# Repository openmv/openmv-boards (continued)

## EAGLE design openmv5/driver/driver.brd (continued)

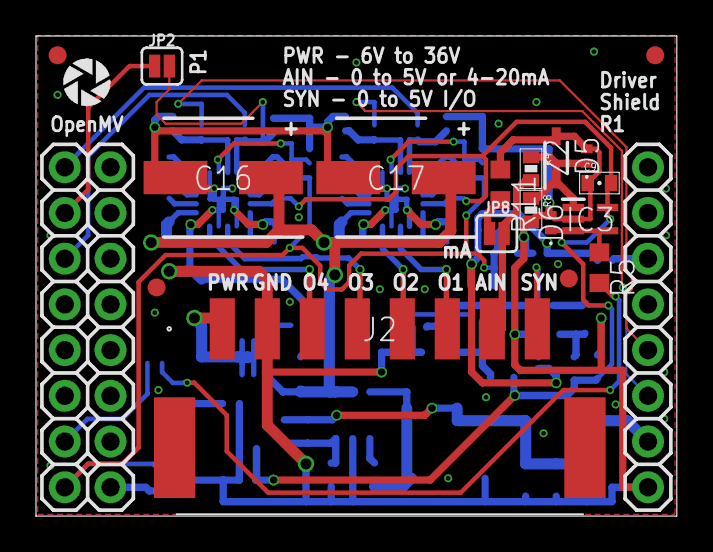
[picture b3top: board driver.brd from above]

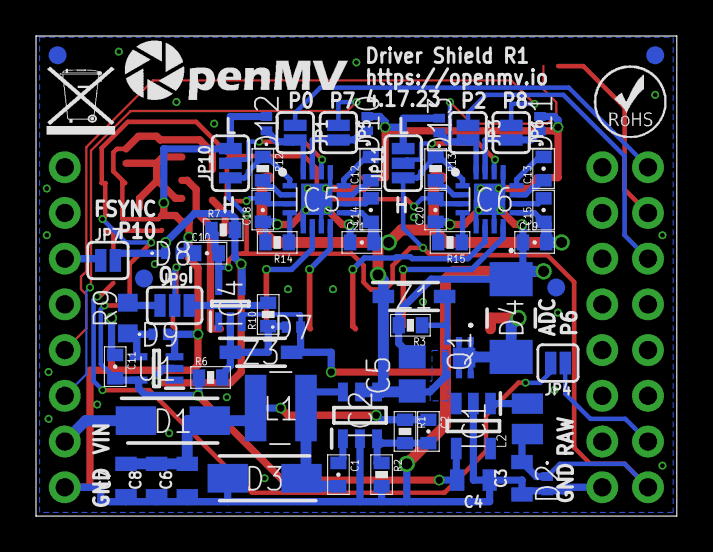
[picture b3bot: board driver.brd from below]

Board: 2 copper layers, 35.6 x 26.7 mm, 87 parts (67 on the bottom side), 50 nets.

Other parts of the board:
U$1: WEEE
U$2: ROHS
U$3: OMV-LOGO
U$9: OPENMV-LOGO

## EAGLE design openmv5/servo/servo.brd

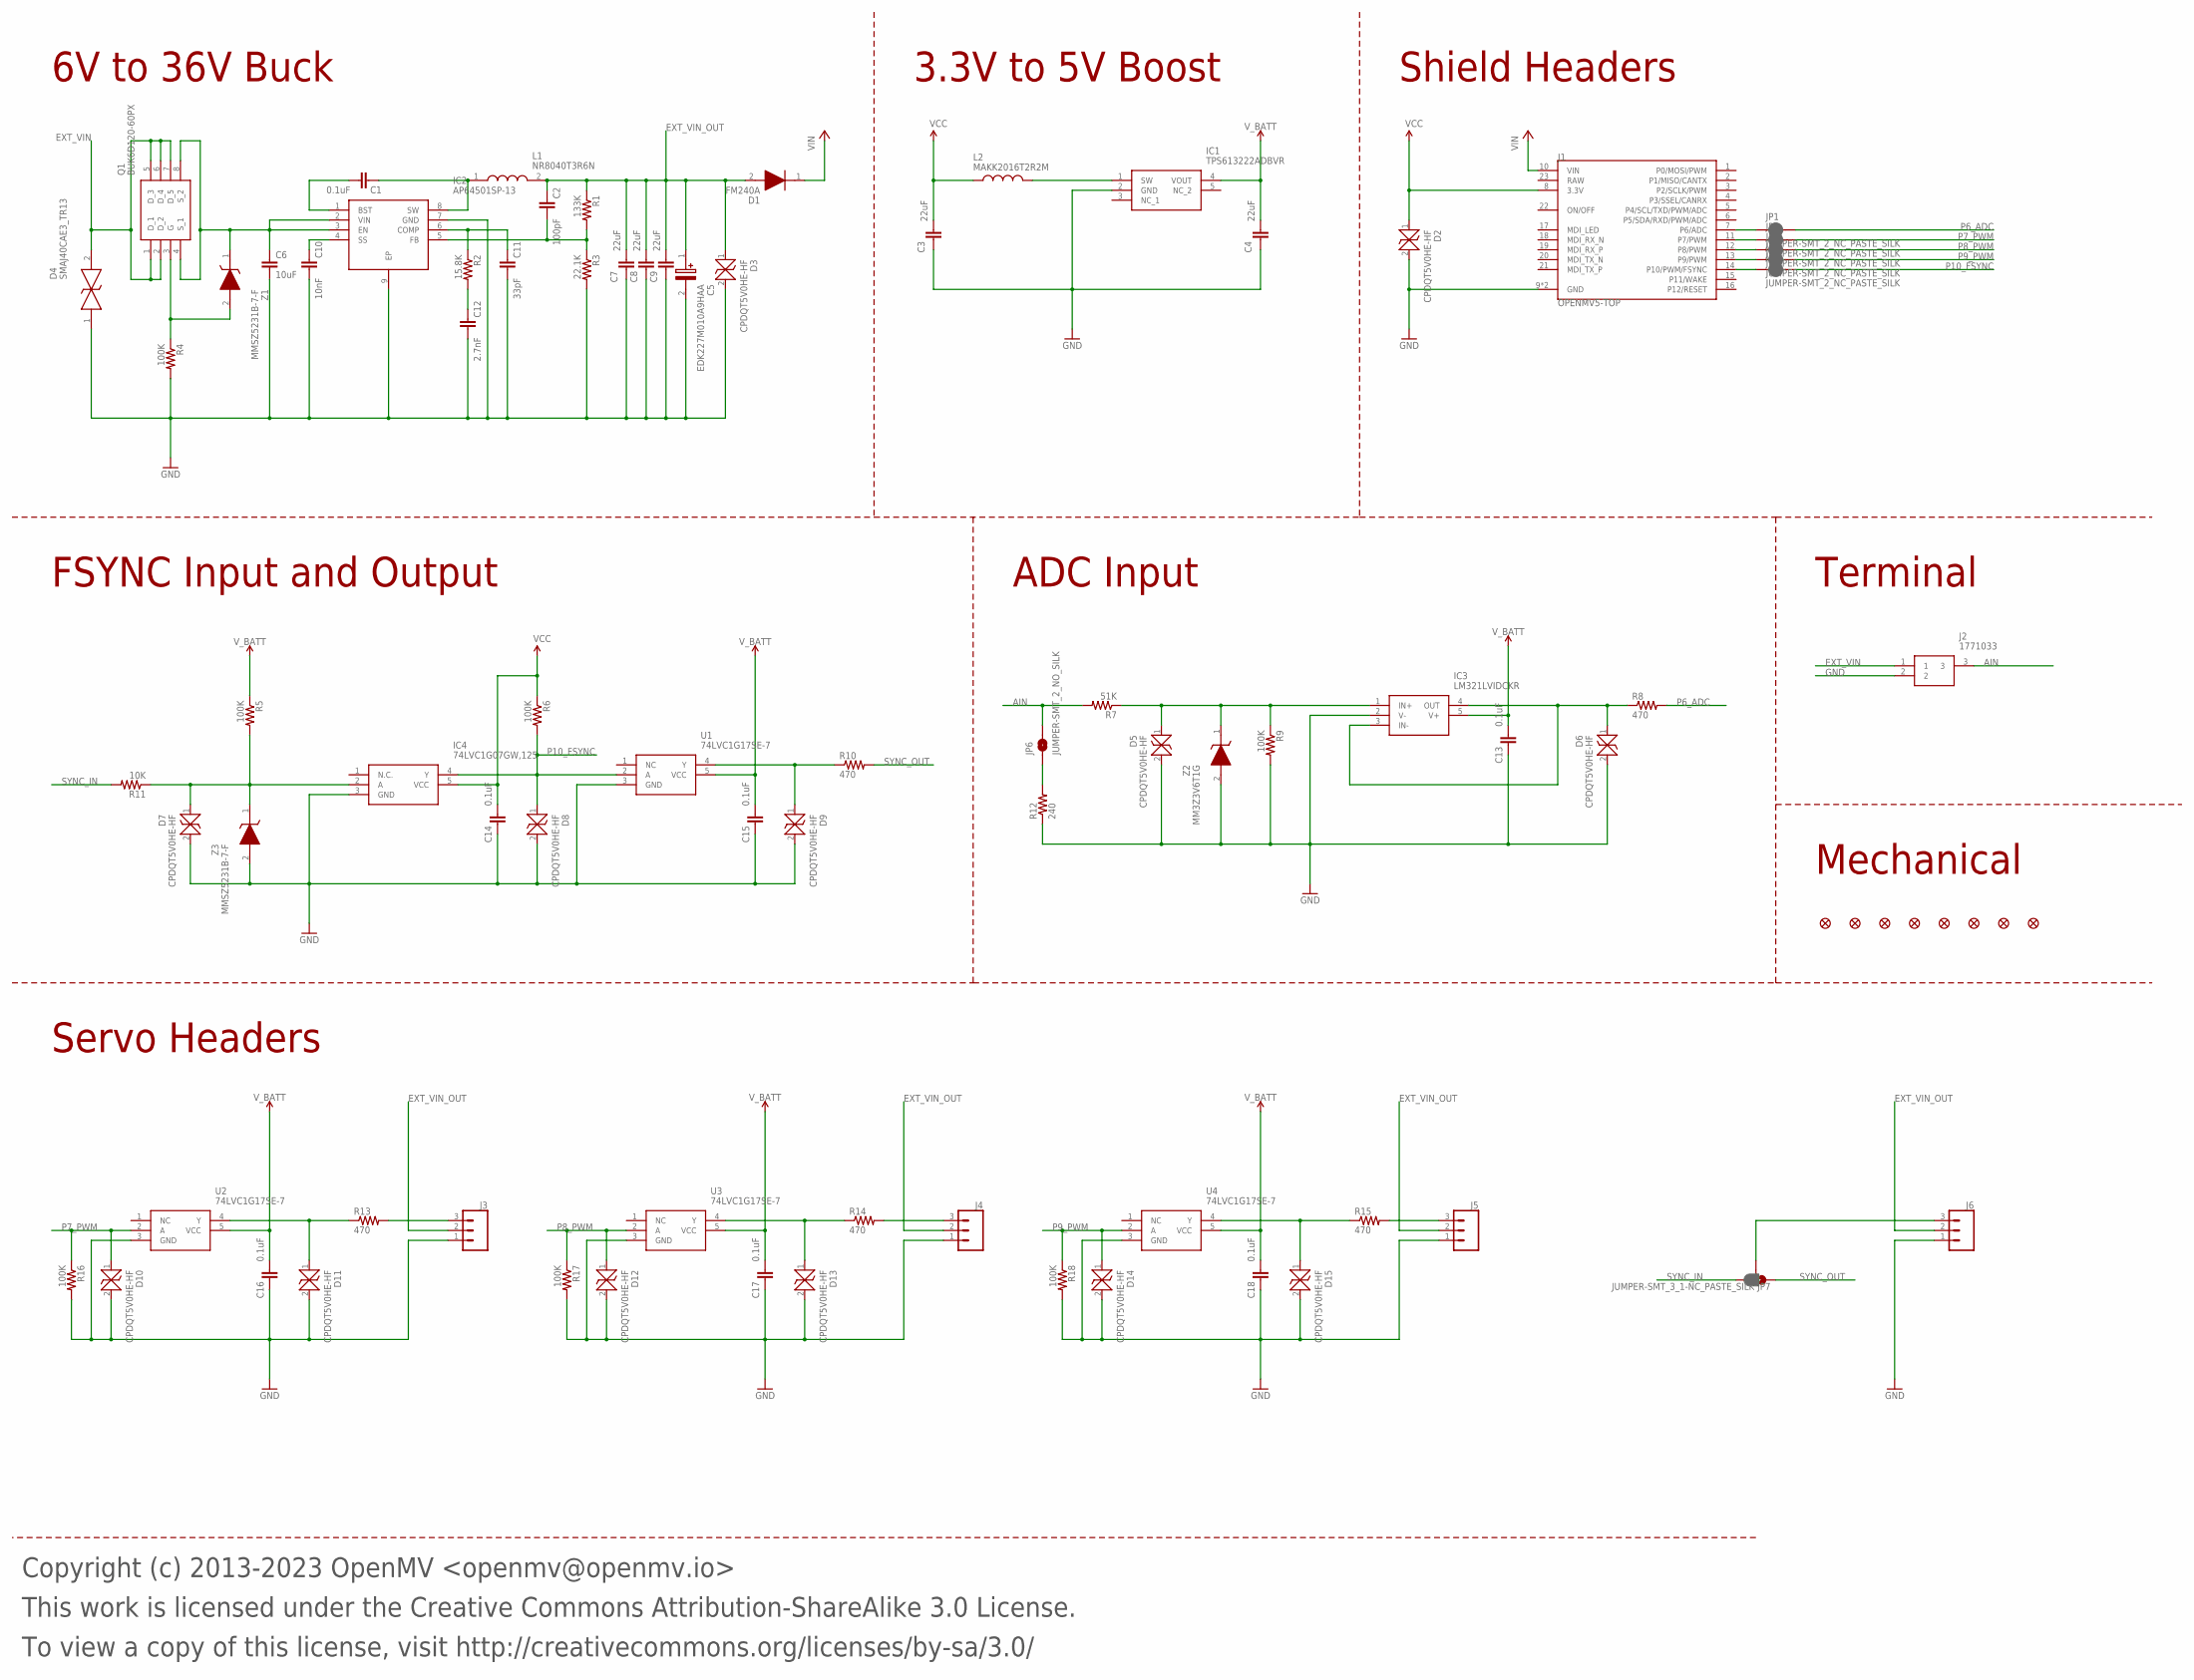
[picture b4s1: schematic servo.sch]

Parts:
C1, C13, C14, C15, C16, C17, C18: 0.1uF; 0402; MPN GRM155R71H104KE14D
C2: 100pF; 0402; MPN CC0402JRNPO9BN101
C3, C4, C7, C8, C9: 22uF; 0805; MPN CL21A226MQQNNNE
C5: EDK227M010A9HAA; CAPAE660X800N; MPN EDK227M010A9HAA
C6: 10uF; C0805; MPN GRM21BR61H106KE43K
C10: 10nF; 0402; MPN CL05B103KB5NNNC
C11: 33pF; 0402; MPN 04025A330JAT2A
C12: 2.7nF; 0402; MPN GCM155R71H272KA37J
D1: FM240A; DIOM5025X231N; MPN FM240A
D2, D3, D5, D6, D7, D8, D9, D10, D11, D12, D13, D14, D15: CPDQT5V0HE-HF; CPDQT5V0HEHF; MPN CPDQT5V0HE-HF
D4: SMAJ40CAE3_TR13; SMAJ40CAE3TR13; MPN SMAJ40CAe3/TR13
FD1, FD2, FD3, FD4, FD5, FD6, FD7, FD8: FIDUCIAL1X2; FIDUCIAL-1X2
IC1: TPS613222ADBVR; SOT95P280X145-5N; MPN TPS613222ADBVR
IC2: AP64501SP-13; SOIC127P600X163-9N; MPN AP64501SP-13
IC3: LM321LVIDCKR; SOT65P210X110-5N; MPN LM321LVIDCKR
IC4: 74LVC1G07GW,125; SOT65P212X110-5N; MPN 74LVC1G07GW,125
J1: OPENMV5-TOP
J2: 1771033; MPN 1771033
J3, J4, J5, J6: CONN_03; 1X03
JP1, JP2, JP3, JP4, JP5: JUMPER-SMT_2_NC_PASTE_SILK; SMT-JUMPER_2_NC_PASTE_SILK
JP6: JUMPER-SMT_2_NO_SILK; SMT-JUMPER_2_NO_SILK
JP7: JUMPER-SMT_3_1-NC_PASTE_SILK; SMT-JUMPER_3_1-NC_PASTE_SILK
L1: NR8040T3R6N; MPN NRS8040T3R6NJGJ
L2: MAKK2016T2R2M; INDC2016X100N; MPN MAKK2016T2R2M
Q1: BUK6D120-60PX; BUK6D12060PX; MPN BUK6D120-60PX
R1: 133K; 0402; MPN RC0402FR-07133KL
R2: 15.8K; 0402; MPN AC0402FR-0715K8L
R3: 22.1K; 0402; MPN CR0402-FX-2212GLF
R4, R5, R6, R9, R16, R17, R18: 100K; 0402; MPN AC0402FR-07100KL
R7: 51K; 0402; MPN RC0402JR-0751KL
R8, R10, R13, R14, R15: 470; R0603; MPN CR0603-FX-4700ELF
R11: 10K; 0402; MPN AC0402FR-1310KL
R12: 240; R0603; MPN RK73B1JTTD241J
U1, U2, U3, U4: 74LVC1G17SE-7; SOT65P210X110-5N; MPN 74LVC1G17SE-7
Z1, Z3: MMSZ5231B-7-F; SOD3716X145N; MPN MMSZ5231B-7-F
Z2: MM3Z3V6T1G; SOD2512X110N; MPN MM3Z3V6T1G

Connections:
AIN: J2.3, JP6.2, R7.2
AIN_INT: D5.1, IC3.1 (IN+), R7.1, R9.1, Z2.1 (K)
AIN_OUT: D6.1, IC3.3 (IN-), IC3.4 (OUT), R8.1
AIN_S: JP6.1, R12.2
EXT_VIN: D4.2, J2.1, Q1.1 (D_1), Q1.2 (D_2), Q1.5 (D_3), Q1.6 (D_4), Q1.7 (D_5)
EXT_VIN_BST: C1.2, IC2.1 (BST)
EXT_VIN_COMP: C11.1, IC2.6 (COMP), R2.1
EXT_VIN_COMP_CAP: C12.1, R2.2
EXT_VIN_FB: C2.2, IC2.5 (FB), R1.2, R3.1
EXT_VIN_G: Q1.3 (G), R4.1, Z1.2 (A)
EXT_VIN_INT: C6.1, IC2.2 (VIN), IC2.3 (EN), Q1.4 (S_1), Q1.8 (S_2), Z1.1 (K)
EXT_VIN_OUT: C2.1, C5.1 (+), C7.2, C8.2, C9.2, D1.2 (A), D3.1, J3.2, J4.2, J5.2, J6.2, L1.2, R1.1
EXT_VIN_SS: C10.1, IC2.4 (SS)
EXT_VIN_SW: C1.1, IC2.8 (SW), L1.1
GND: C3.1, C4.1, C5.2 (-), C6.2, C7.1, C8.1, C9.1, C10.2, C11.2, C12.2, C13.1, C14.1, C15.1, C16.1, C17.1, C18.1, D2.2, D3.2, D4.1, D5.2, D6.2, D7.2, D8.2, D9.2, D10.2, D11.2, D12.2, D13.2, D14.2, D15.2, IC1.2 (GND), IC2.7 (GND), IC2.9 (EP), IC3.2 (V-), IC4.3 (GND), J1.9 (GND), J1.24 (GND), J2.2, J3.1, J4.1, J5.1, J6.1, R3.2, R4.2, R9.2, R12.1, R16.2, R17.2, R18.2, U1.3 (GND), U2.3 (GND), U3.3 (GND), U4.3 (GND), Z2.2 (A), Z3.2 (A)
P6_ADC: JP1.2, R8.2
P6_ADC_INT: J1.7 (P6/ADC), JP1.1
P7_PWM: D10.1, JP2.2, R16.1, U2.2 (A)
P7_PWM_INT: J1.11 (P7/PWM), JP2.1
P7_PWM_SERVO: J3.3, R13.2
P7_PWM_SERVO_INT: D11.1, R13.1, U2.4 (Y)
P8_PWM: D12.1, JP3.2, R17.1, U3.2 (A)
P8_PWM_INT: J1.12 (P8/PWM), JP3.1
P8_PWM_SERVO: J4.3, R14.2
P8_PWM_SERVO_INT: D13.1, R14.1, U3.4 (Y)
P9_PWM: D14.1, JP4.2, R18.1, U4.2 (A)
P9_PWM_INT: J1.13 (P9/PWM), JP4.1
P9_PWM_SERVO: J5.3, R15.2
P9_PWM_SERVO_INT: D15.1, R15.1, U4.4 (Y)
P10_FSYNC: D8.1, IC4.4 (Y), JP5.2, R6.2, U1.2 (A)
P10_FSYNC_INT: J1.14 (P10/PWM/FSYNC), JP5.1
SW: IC1.1 (SW), L2.2
SYNC: J6.3, JP7.2
SYNC_IN: JP7.3, R11.2
SYNC_IN_INT: D7.1, IC4.2 (A), R5.2, R11.1, Z3.1 (K)
SYNC_OUT: JP7.1, R10.2
SYNC_OUT_INT: D9.1, R10.1, U1.4 (Y)
VCC: C3.2, C14.2, D2.1, IC4.5 (VCC), J1.8 (3.3V), L2.1, R6.1
VIN: D1.1 (K), J1.10 (VIN)
V_BATT: C4.2, C13.2, C15.2, C16.2, C17.2, C18.2, IC1.4 (VOUT), IC3.5 (V+), R5.1, U1.5 (VCC), U2.5 (VCC), U3.5 (VCC), U4.5 (VCC)

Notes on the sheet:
Copyright (c) 2013-2023 OpenMV <openmv@openmv.io>
This work is licensed under the Creative Commons Attribution-ShareAlike 3.0 License.
To view a copy of this license, visit http://creativecommons.org/licenses/by-sa/3.0/
FSYNC Input and Output
Mechanical
Shield Headers
6V to 36V Buck
3.3V to 5V Boost
Terminal
ADC Input
Servo Headers

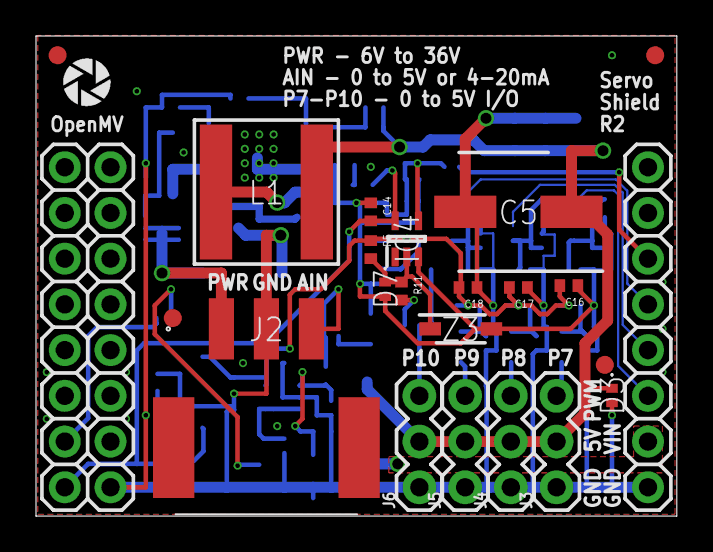
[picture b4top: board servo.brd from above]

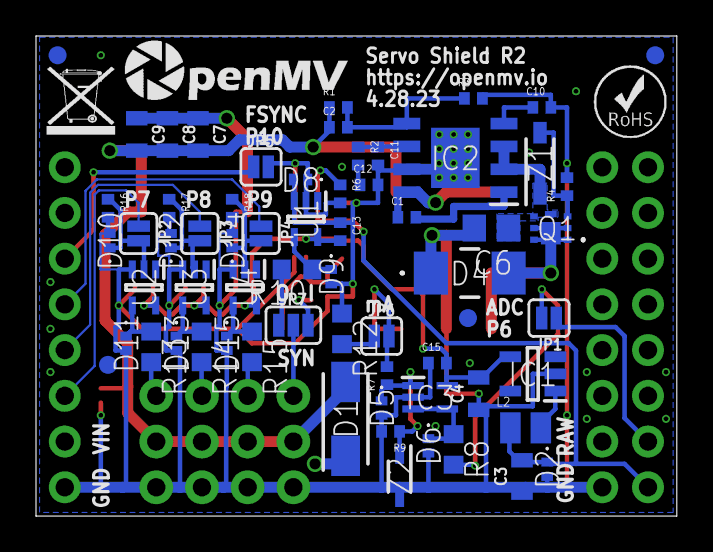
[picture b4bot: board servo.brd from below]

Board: 2 copper layers, 35.6 x 26.7 mm, 90 parts (67 on the bottom side), 40 nets.

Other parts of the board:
U$1: WEEE
U$2: ROHS
U$3: OMV-LOGO
U$9: OPENMV-LOGO

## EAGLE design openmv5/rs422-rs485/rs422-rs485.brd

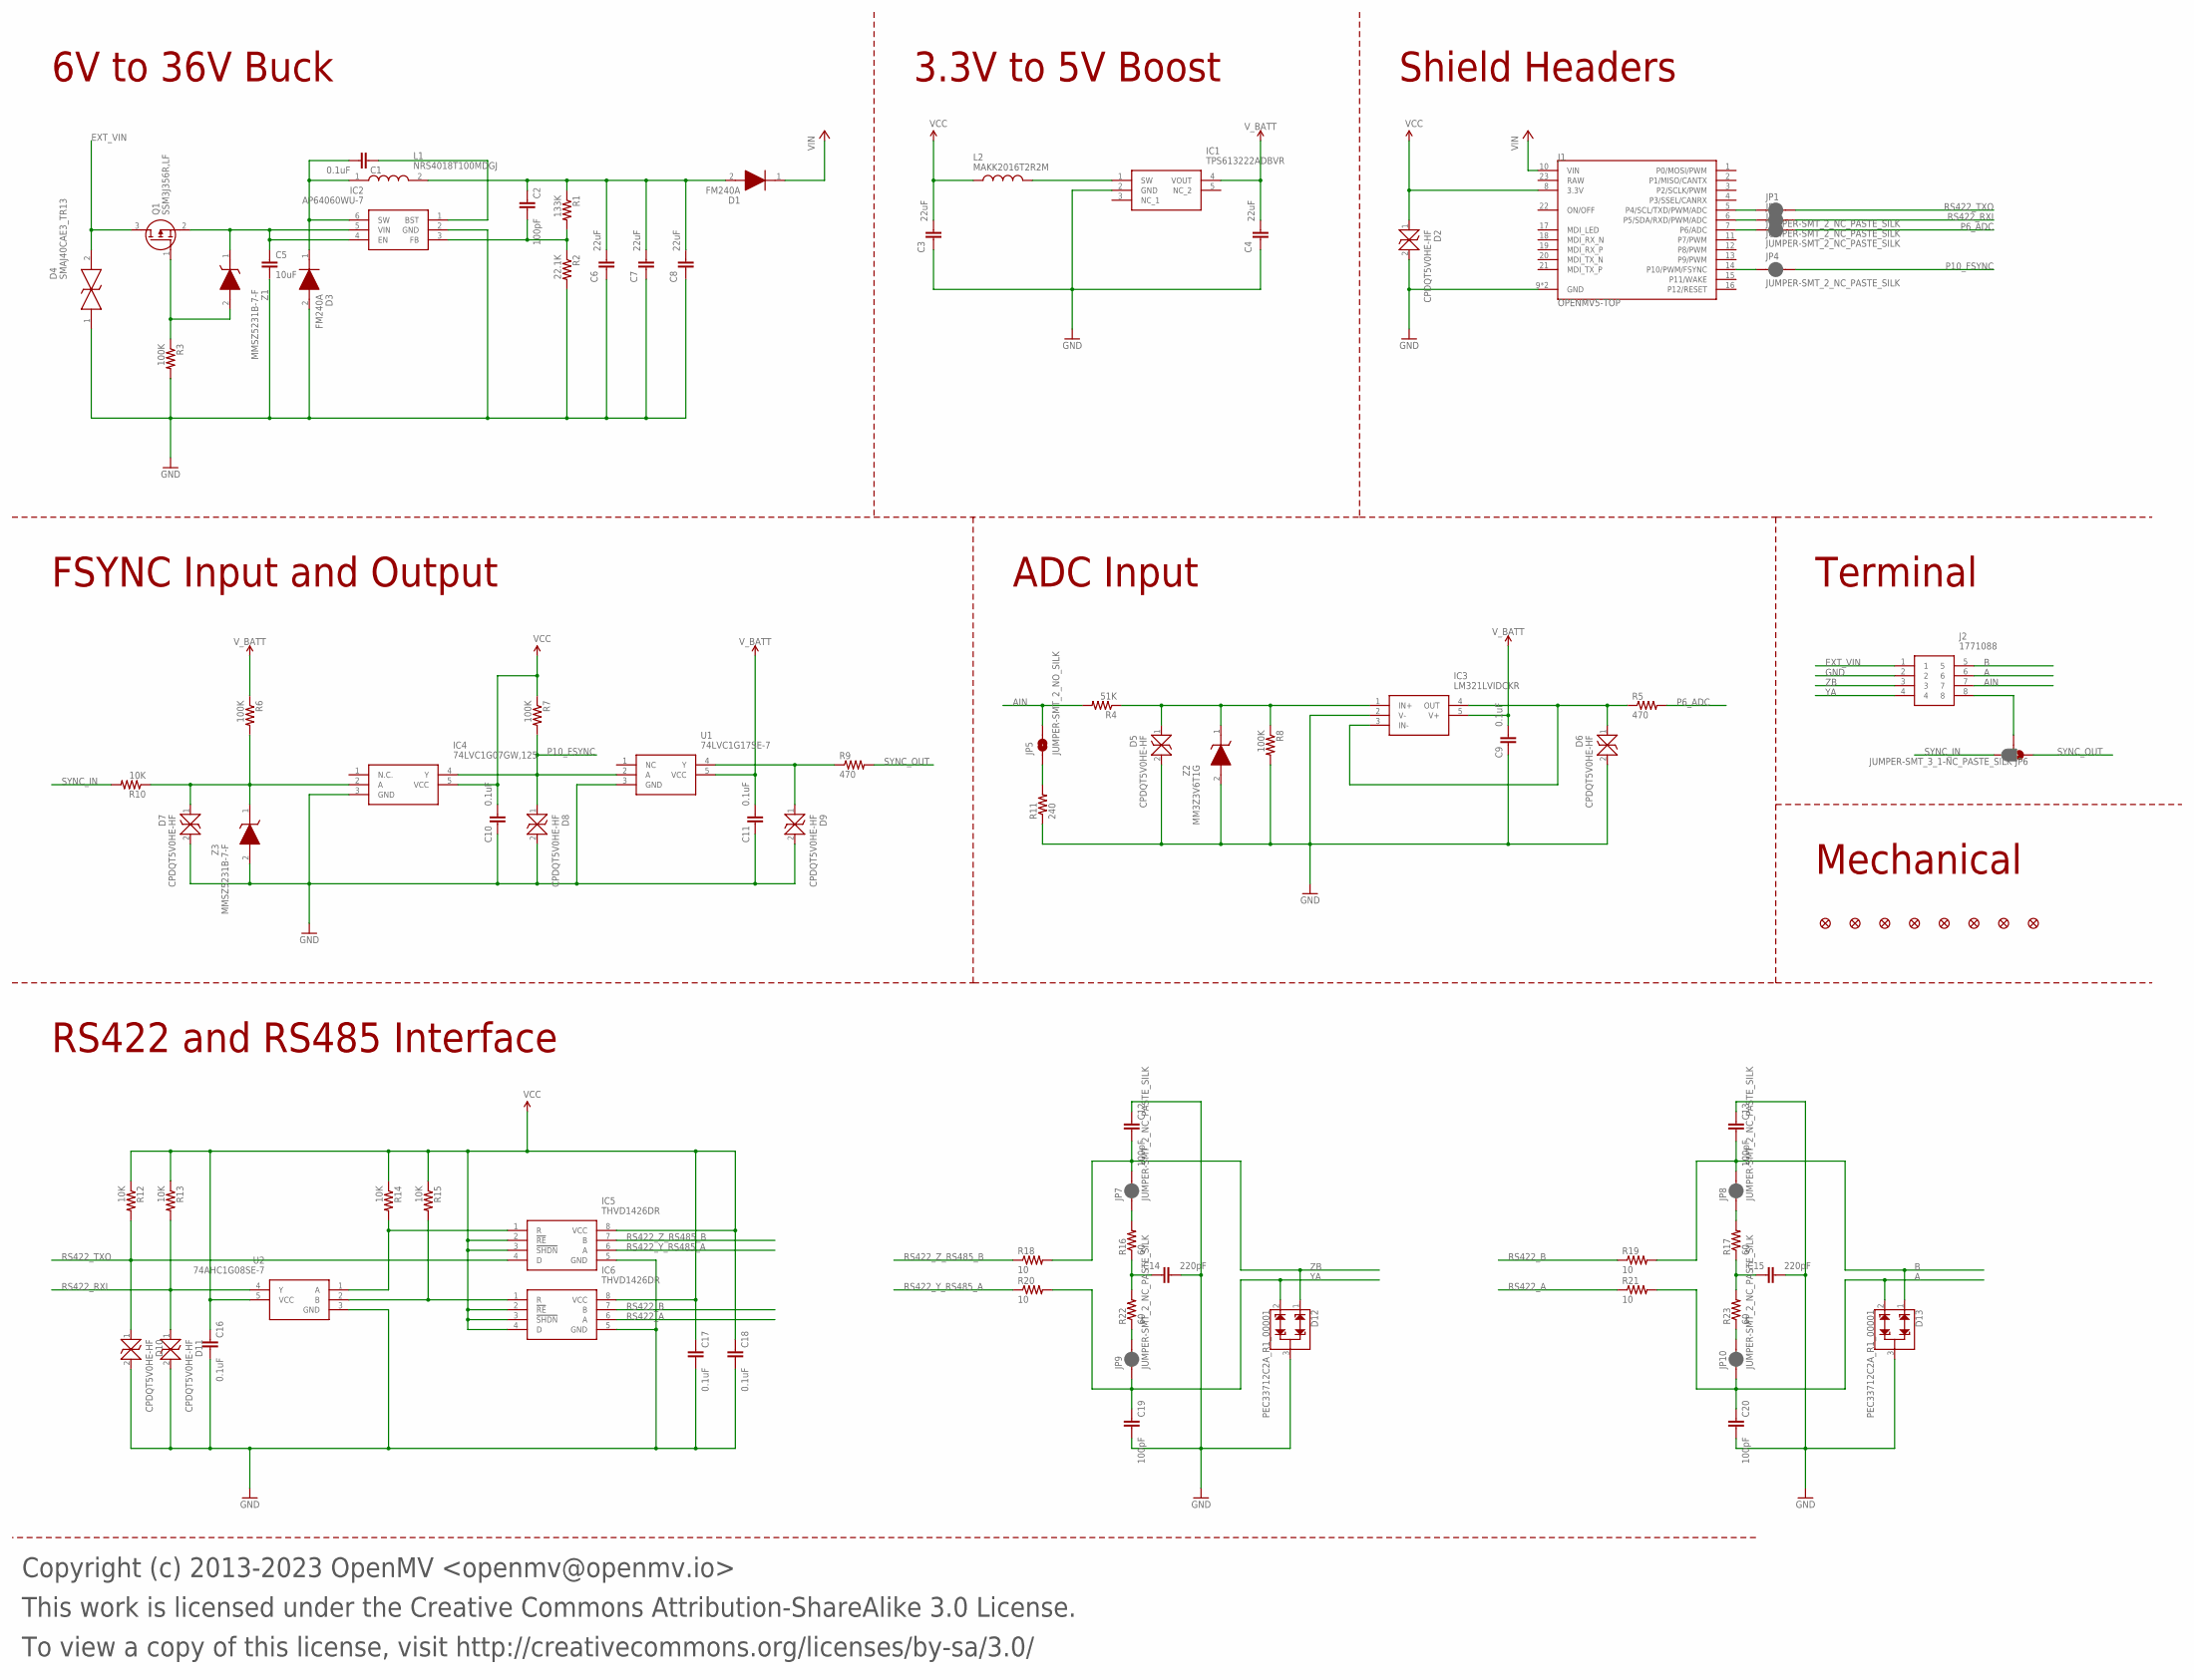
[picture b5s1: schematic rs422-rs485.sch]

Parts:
C1, C9, C10, C11, C16, C17, C18: 0.1uF; 0402-CAP; MPN GRM155R71H104KE14D
C2, C12, C13, C19, C20: 100pF; 0402-CAP; MPN CC0402JRNPO9BN101
C3, C4, C6, C7, C8: 22uF; 0805; MPN CL21A226MQQNNNE
C5: 10uF; C0805; MPN GRM21BR61H106KE43K
C14, C15: 220pF; 0402-CAP; MPN 0402B221K500CT
D1, D3: FM240A; DIOM5025X231N; MPN FM240A
D2, D5, D6, D7, D8, D9, D10, D11: CPDQT5V0HE-HF; CPDQT5V0HEHF; MPN CPDQT5V0HE-HF
D4: SMAJ40CAE3_TR13; SMAJ40CAE3TR13; MPN SMAJ40CAe3/TR13
D12, D13: PEC33712C2A_R1_00001; SOT23-3; MPN PEC33712C2A_R1_00001
FD1, FD2, FD3, FD4, FD5, FD6, FD7, FD8: FIDUCIAL1X2; FIDUCIAL-1X2
IC1: TPS613222ADBVR; SOT95P280X145-5N; MPN TPS613222ADBVR
IC2: AP64060WU-7; SOT95P280X100-6N; MPN AP64060WU-7
IC3: LM321LVIDCKR; SOT65P210X110-5N; MPN LM321LVIDCKR
IC4: 74LVC1G07GW,125; SOT65P212X110-5N; MPN 74LVC1G07GW,125
IC5, IC6: THVD1426DR; SOIC127P600X175-8N; MPN THVD1426DR
J1: OPENMV5-TOP
J2: 1771088; MPN 1771088
JP1, JP2, JP3, JP4, JP7, JP8, JP9, JP10: JUMPER-SMT_2_NC_PASTE_SILK; SMT-JUMPER_2_NC_PASTE_SILK
JP5: JUMPER-SMT_2_NO_SILK; SMT-JUMPER_2_NO_SILK
JP6: JUMPER-SMT_3_1-NC_PASTE_SILK; SMT-JUMPER_3_1-NC_PASTE_SILK
L1: NRS4018T100MDGJ; MPN NRS4018T100MDGJ
L2: MAKK2016T2R2M; INDC2016X100N; MPN MAKK2016T2R2M
Q1: SSM3J356R,LF; SOTFL95P240X88-3N; MPN SSM3J356R,LF
R1: 133K; 0402-RES; MPN RC0402FR-07133KL
R2: 22.1K; 0402-RES; MPN CR0402-FX-2212GLF
R3, R6, R7, R8: 100K; 0402-RES; MPN AC0402FR-07100KL
R4: 51K; 0402-RES; MPN RC0402JR-0751KL
R5, R9: 470; R0603; MPN CR0603-FX-4700ELF
R10, R12, R13, R14, R15: 10K; 0402-RES; MPN AC0402FR-1310KL
R11: 240; R0603; MPN RK73B1JTTD241J
R16, R17, R22, R23: 60; R1206; MPN RC1206FR-0760R4L
R18, R19, R20, R21: 10; R0805; MPN RK73B2ATTD100J
U1: 74LVC1G17SE-7; SOT65P210X110-5N; MPN 74LVC1G17SE-7
U2: 74AHC1G08SE-7; SOT65P210X110-5N; MPN 74AHC1G08SE-7
Z1, Z3: MMSZ5231B-7-F; SOD3716X145N; MPN MMSZ5231B-7-F
Z2: MM3Z3V6T1G; SOD2512X110N; MPN MM3Z3V6T1G

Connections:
A: C20.1, D13.2, J2.6, JP10.1, R21.2
AIN: J2.7, JP5.2, R4.2
AIN_INT: D5.1, IC3.1 (IN+), R4.1, R8.1, Z2.1 (K)
AIN_OUT: D6.1, IC3.3 (IN-), IC3.4 (OUT), R5.1
AIN_S: JP5.1, R11.2
A_J: JP10.2, R23.1
B: C13.2, D13.1, J2.5, JP8.2, R19.2
B_J: JP8.1, R17.2
EXT_VIN: D4.2, J2.1, Q1.3 (D)
EXT_VIN_BST: C1.1, IC2.1 (BST)
EXT_VIN_FB: C2.2, IC2.3 (FB), R1.2, R2.1
EXT_VIN_G: Q1.1 (G), R3.1, Z1.2 (A)
EXT_VIN_INT: C5.1, IC2.4 (EN), IC2.5 (VIN), Q1.2 (S), Z1.1 (K)
EXT_VIN_OUT: C2.1, C6.2, C7.2, C8.2, D1.2 (A), L1.2, R1.1
EXT_VIN_SW: C1.2, D3.1 (K), IC2.6 (SW), L1.1
GND: C3.1, C4.1, C5.2, C6.1, C7.1, C8.1, C9.1, C10.1, C11.1, C12.1, C13.1, C14.2, C15.2, C16.2, C17.2, C18.2, C19.2, C20.2, D2.2, D3.2 (A), D4.1, D5.2, D6.2, D7.2, D8.2, D9.2, D10.2, D11.2, D12.3, D13.3, IC1.2 (GND), IC2.2 (GND), IC3.2 (V-), IC4.3 (GND), IC5.5 (GND), IC6.5 (GND), J1.9 (GND), J1.24 (GND), J2.2, R2.2, R3.2, R8.2, R11.1, U1.3 (GND), U2.3 (GND), Z2.2 (A), Z3.2 (A)
P6_ADC: JP3.2, R5.2
P6_ADC_INT: J1.7 (P6/ADC), JP3.1
P10_FSYNC: D8.1, IC4.4 (Y), JP4.2, R7.2, U1.2 (A)
P10_FSYNC_INT: J1.14 (P10/PWM/FSYNC), JP4.1
RA: IC5.1 (R), R14.2, U2.1 (A)
RB: IC6.1 (R), R15.2, U2.2 (B)
RS232_RXI_INT: J1.6 (P5/SDA/RXD/PWM/ADC), JP2.1
RS232_TXO_INT: J1.5 (P4/SCL/TXD/PWM/ADC), JP1.1
RS422_A: IC6.6 (A), R21.1
RS422_B: IC6.7 (B), R19.1
RS422_RXI: D11.1, JP2.2, R13.2, U2.4 (Y)
RS422_S: C15.1, R17.1, R23.2
RS422_TXO: D10.1, IC5.4 (D), JP1.2, R12.2
RS422_Y_RS485_A: IC5.6 (A), R20.1
RS422_Z_RS485_B: IC5.7 (B), R18.1
RS485_S: C14.1, R16.1, R22.2
SW: IC1.1 (SW), L2.2
SYNC: J2.8, JP6.2
SYNC_IN: JP6.3, R10.2
SYNC_IN_INT: D7.1, IC4.2 (A), R6.2, R10.1, Z3.1 (K)
SYNC_OUT: JP6.1, R9.2
SYNC_OUT_INT: D9.1, R9.1, U1.4 (Y)
VCC: C3.2, C10.2, C16.1, C17.1, C18.1, D2.1, IC4.5 (VCC), IC5.2 (!RE), IC5.3 (!SHDN), IC5.8 (VCC), IC6.2 (!RE), IC6.3 (!SHDN), IC6.4 (D), IC6.8 (VCC), J1.8 (3.3V), L2.1, R7.1, R12.1, R13.1, R14.1, R15.1, U2.5 (VCC)
VIN: D1.1 (K), J1.10 (VIN)
V_BATT: C4.2, C9.2, C11.2, IC1.4 (VOUT), IC3.5 (V+), R6.1, U1.5 (VCC)
YA: C19.1, D12.2, J2.4, JP9.1, R20.2
YA_J: JP9.2, R22.1
YB_J: JP7.1, R16.2
ZB: C12.2, D12.1, J2.3, JP7.2, R18.2

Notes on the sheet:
Copyright (c) 2013-2023 OpenMV <openmv@openmv.io>
This work is licensed under the Creative Commons Attribution-ShareAlike 3.0 License.
To view a copy of this license, visit http://creativecommons.org/licenses/by-sa/3.0/
FSYNC Input and Output
Mechanical
Shield Headers
6V to 36V Buck
3.3V to 5V Boost
RS422 and RS485 Interface
Terminal
ADC Input

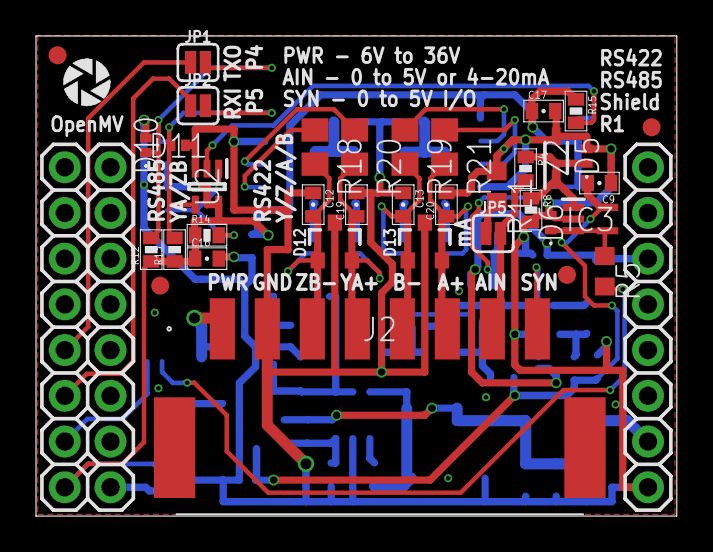
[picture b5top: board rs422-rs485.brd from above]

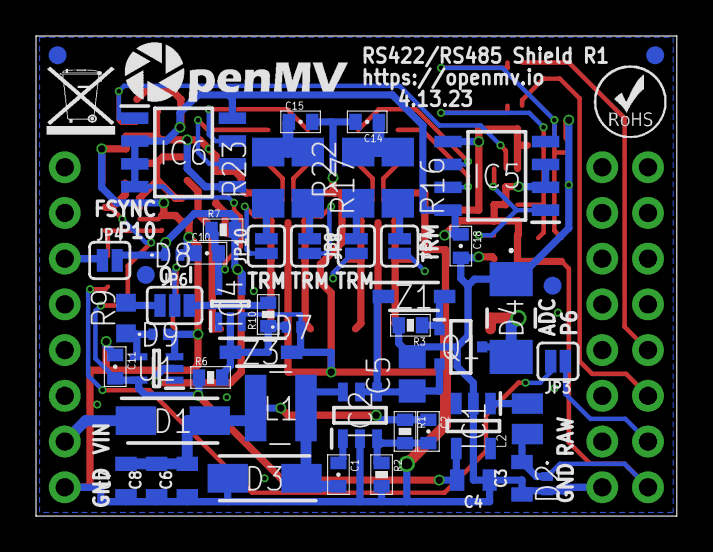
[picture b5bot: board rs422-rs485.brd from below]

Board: 2 copper layers, 35.6 x 26.7 mm, 94 parts (56 on the bottom side), 45 nets.

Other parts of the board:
U$1: WEEE
U$2: ROHS
U$3: OMV-LOGO
U$9: OPENMV-LOGO

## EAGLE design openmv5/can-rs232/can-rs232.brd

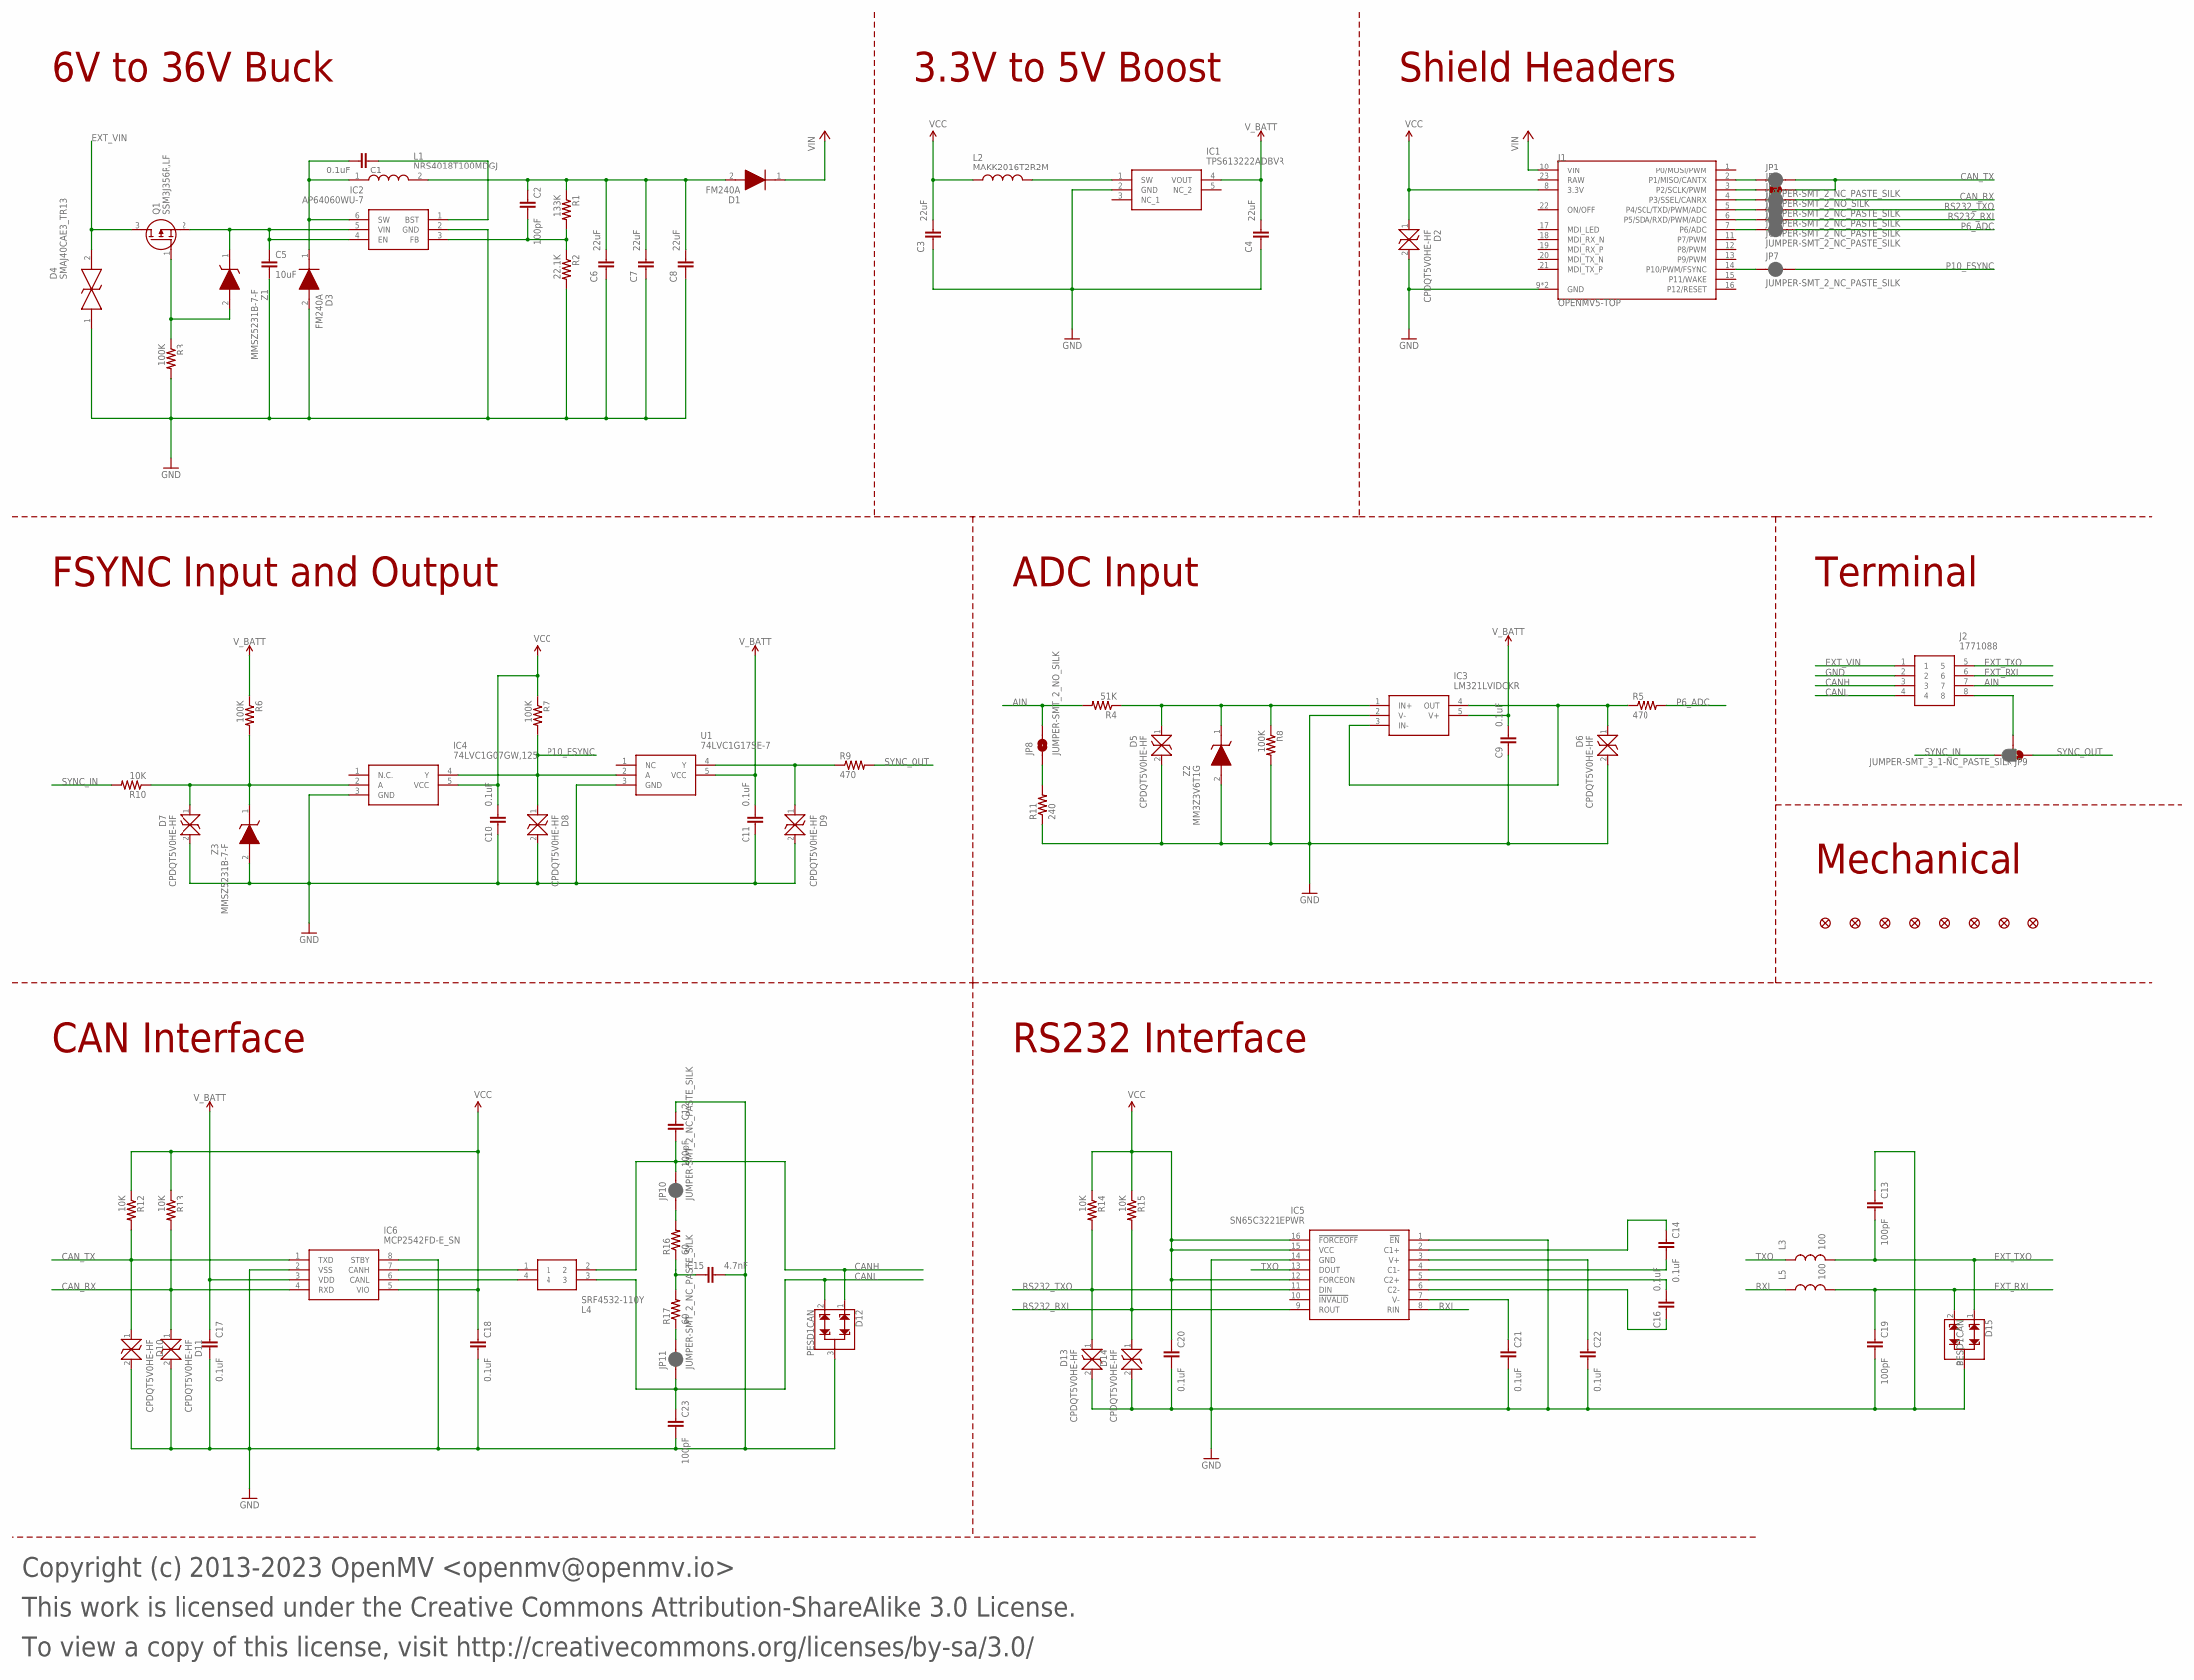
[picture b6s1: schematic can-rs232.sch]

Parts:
C1, C9, C10, C11, C14, C16, C17, C18, C20, C21, C22: 0.1uF; 0402-CAP; MPN GRM155R71H104KE14D
C2, C12, C13, C19, C23: 100pF; 0402-CAP; MPN CC0402JRNPO9BN101
C3, C4, C6, C7, C8: 22uF; 0805; MPN CL21A226MQQNNNE
C5: 10uF; C0805; MPN GRM21BR61H106KE43K
C15: 4.7nF; 0402-CAP; MPN GRM155R71H472JA01D
D1, D3: FM240A; DIOM5025X231N; MPN FM240A
D2, D5, D6, D7, D8, D9, D10, D11, D13, D14: CPDQT5V0HE-HF; CPDQT5V0HEHF; MPN CPDQT5V0HE-HF
D4: SMAJ40CAE3_TR13; SMAJ40CAE3TR13; MPN SMAJ40CAe3/TR13
D12, D15: PESD1CAN; SOT23-3; MPN VCAN36A2-03S-E3-08
FD1, FD2, FD3, FD4, FD5, FD6, FD7, FD8: FIDUCIAL1X2; FIDUCIAL-1X2
IC1: TPS613222ADBVR; SOT95P280X145-5N; MPN TPS613222ADBVR
IC2: AP64060WU-7; SOT95P280X100-6N; MPN AP64060WU-7
IC3: LM321LVIDCKR; SOT65P210X110-5N; MPN LM321LVIDCKR
IC4: 74LVC1G07GW,125; SOT65P212X110-5N; MPN 74LVC1G07GW,125
IC5: SN65C3221EPWR; SOP65P640X120-16N; MPN SN65C3221EPWR
IC6: MCP2542FD-E_SN; SOIC127P600X175-8N; MPN MCP2542FD-E/SN
J1: OPENMV5-TOP
J2: 1771088; MPN 1771088
JP1, JP3, JP4, JP5, JP6, JP7, JP10, JP11: JUMPER-SMT_2_NC_PASTE_SILK; SMT-JUMPER_2_NC_PASTE_SILK
JP2, JP8: JUMPER-SMT_2_NO_SILK; SMT-JUMPER_2_NO_SILK
JP9: JUMPER-SMT_3_1-NC_PASTE_SILK; SMT-JUMPER_3_1-NC_PASTE_SILK
L1: NRS4018T100MDGJ; MPN NRS4018T100MDGJ
L2: MAKK2016T2R2M; INDC2016X100N; MPN MAKK2016T2R2M
L3, L5: 100; C0402; MPN MFBM1V1005-101-R
L4: SRF4532-110Y; SRF4532101Y; MPN SRF4532-110Y
Q1: SSM3J356R,LF; SOTFL95P240X88-3N; MPN SSM3J356R,LF
R1: 133K; 0402-RES; MPN RC0402FR-07133KL
R2: 22.1K; 0402-RES; MPN CR0402-FX-2212GLF
R3, R6, R7, R8: 100K; 0402-RES; MPN AC0402FR-07100KL
R4: 51K; 0402-RES; MPN RC0402JR-0751KL
R5, R9: 470; R0603; MPN CR0603-FX-4700ELF
R10, R12, R13, R14, R15: 10K; 0402-RES; MPN AC0402FR-1310KL
R11: 240; R0603; MPN RK73B1JTTD241J
R16, R17: 60; R1206; MPN RC1206FR-0760R4L
U1: 74LVC1G17SE-7; SOT65P210X110-5N; MPN 74LVC1G17SE-7
Z1, Z3: MMSZ5231B-7-F; SOD3716X145N; MPN MMSZ5231B-7-F
Z2: MM3Z3V6T1G; SOD2512X110N; MPN MM3Z3V6T1G

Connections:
AIN: J2.7, JP8.2, R4.2
AIN_INT: D5.1, IC3.1 (IN+), R4.1, R8.1, Z2.1 (K)
AIN_OUT: D6.1, IC3.3 (IN-), IC3.4 (OUT), R5.1
AIN_S: JP8.1, R11.2
C1+: C14.1, IC5.2 (C1+)
C1-: C14.2, IC5.4 (C1-)
C2+: C16.2, IC5.5 (C2+)
C2-: C16.1, IC5.6 (C2-)
CANH: C12.2, D12.1, J2.3, JP10.2, L4.2
CANH_INT: IC6.7 (CANH), L4.1
CANH_J: JP10.1, R16.2
CANL: C23.1, D12.2, J2.4, JP11.1, L4.3
CANL_INT: IC6.6 (CANL), L4.4
CANL_J: JP11.2, R17.1
CAN_RX: D11.1, IC6.4 (RXD), JP3.2, R13.2
CAN_RX_INT: J1.4 (P3/SSEL/CANRX), JP3.1
CAN_S: C15.1, R16.1, R17.2
CAN_TX: D10.1, IC6.1 (TXD), JP1.2, JP2.2, R12.2
CAN_TX_INT: J1.2 (P1/MISO/CANTX), JP1.1
CAN_TX_INT_2: J1.3 (P2/SCLK/PWM), JP2.1
EXT_RXI: C19.1, D15.2, J2.6, L5.2
EXT_TXO: C13.2, D15.1, J2.5, L3.2
EXT_VIN: D4.2, J2.1, Q1.3 (D)
EXT_VIN_BST: C1.1, IC2.1 (BST)
EXT_VIN_FB: C2.2, IC2.3 (FB), R1.2, R2.1
EXT_VIN_G: Q1.1 (G), R3.1, Z1.2 (A)
EXT_VIN_INT: C5.1, IC2.4 (EN), IC2.5 (VIN), Q1.2 (S), Z1.1 (K)
EXT_VIN_OUT: C2.1, C6.2, C7.2, C8.2, D1.2 (A), L1.2, R1.1
EXT_VIN_SW: C1.2, D3.1 (K), IC2.6 (SW), L1.1
GND: C3.1, C4.1, C5.2, C6.1, C7.1, C8.1, C9.1, C10.1, C11.1, C12.1, C13.1, C15.2, C17.2, C18.2, C19.2, C20.2, C21.2, C22.2, C23.2, D2.2, D3.2 (A), D4.1, D5.2, D6.2, D7.2, D8.2, D9.2, D10.2, D11.2, D12.3, D13.2, D14.2, D15.3, IC1.2 (GND), IC2.2 (GND), IC3.2 (V-), IC4.3 (GND), IC5.1 (!EN), IC5.14 (GND), IC6.2 (VSS), IC6.8 (STBY), J1.9 (GND), J1.24 (GND), J2.2, R2.2, R3.2, R8.2, R11.1, U1.3 (GND), Z2.2 (A), Z3.2 (A)
P6_ADC: JP6.2, R5.2
P6_ADC_INT: J1.7 (P6/ADC), JP6.1
P10_FSYNC: D8.1, IC4.4 (Y), JP7.2, R7.2, U1.2 (A)
P10_FSYNC_INT: J1.14 (P10/PWM/FSYNC), JP7.1
RS232_RXI: D14.1, IC5.9 (ROUT), JP5.2, R15.2
RS232_RXI_INT: J1.6 (P5/SDA/RXD/PWM/ADC), JP5.1
RS232_TXO: D13.1, IC5.11 (DIN), JP4.2, R14.2
RS232_TXO_INT: J1.5 (P4/SCL/TXD/PWM/ADC), JP4.1
RXI: IC5.8 (RIN), L5.1
SW: IC1.1 (SW), L2.2
SYNC: J2.8, JP9.2
SYNC_IN: JP9.3, R10.2
SYNC_IN_INT: D7.1, IC4.2 (A), R6.2, R10.1, Z3.1 (K)
SYNC_OUT: JP9.1, R9.2
SYNC_OUT_INT: D9.1, R9.1, U1.4 (Y)
TXO: IC5.13 (DOUT), L3.1
V+: C22.1, IC5.3 (V+)
V-: C21.1, IC5.7 (V-)
VCC: C3.2, C10.2, C18.1, C20.1, D2.1, IC4.5 (VCC), IC5.12 (FORCEON), IC5.15 (VCC), IC5.16 (!FORCEOFF), IC6.5 (VIO), J1.8 (3.3V), L2.1, R7.1, R12.1, R13.1, R14.1, R15.1
VIN: D1.1 (K), J1.10 (VIN)
V_BATT: C4.2, C9.2, C11.2, C17.1, IC1.4 (VOUT), IC3.5 (V+), IC6.3 (VDD), R6.1, U1.5 (VCC)

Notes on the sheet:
Copyright (c) 2013-2023 OpenMV <openmv@openmv.io>
This work is licensed under the Creative Commons Attribution-ShareAlike 3.0 License.
To view a copy of this license, visit http://creativecommons.org/licenses/by-sa/3.0/
FSYNC Input and Output
Mechanical
Shield Headers
6V to 36V Buck
3.3V to 5V Boost
CAN Interface
RS232 Interface
Terminal
ADC Input

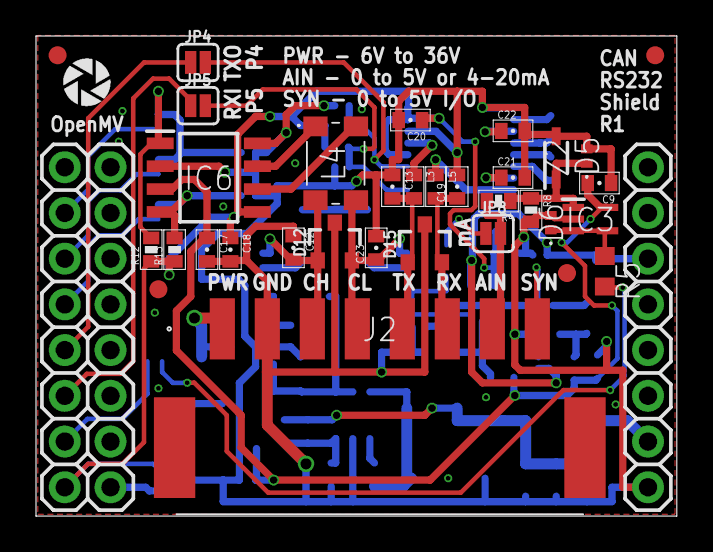
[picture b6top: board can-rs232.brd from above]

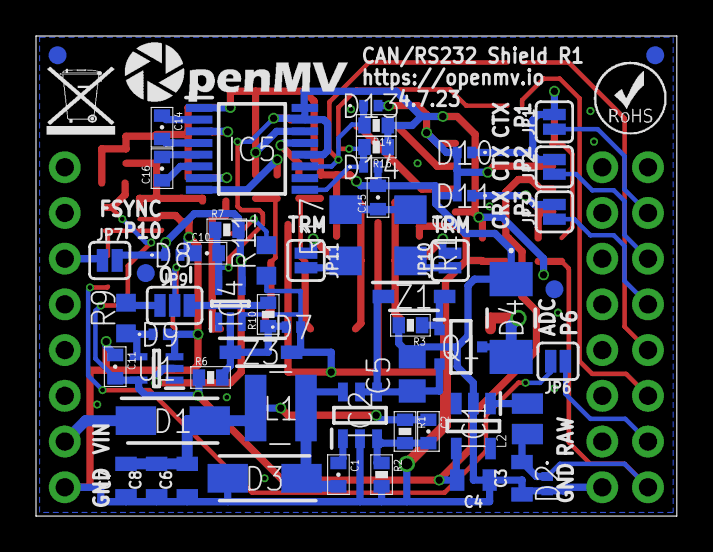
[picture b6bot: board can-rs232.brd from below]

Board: 2 copper layers, 35.6 x 26.7 mm, 96 parts (61 on the bottom side), 51 nets.

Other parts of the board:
U$1: WEEE
U$2: ROHS
U$3: OMV-LOGO
U$9: OPENMV-LOGO
